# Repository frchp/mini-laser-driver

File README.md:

# mini-laser-driver

## Goal
300mA capable constant current source driver for laser diode application.

## Repository

[hw](hw/) : Hardware sources

[sim](sim/) : LTSpice simulation

[doc](doc/) : Useful documentation

[results](results/) : Measurements

## Results
TODO

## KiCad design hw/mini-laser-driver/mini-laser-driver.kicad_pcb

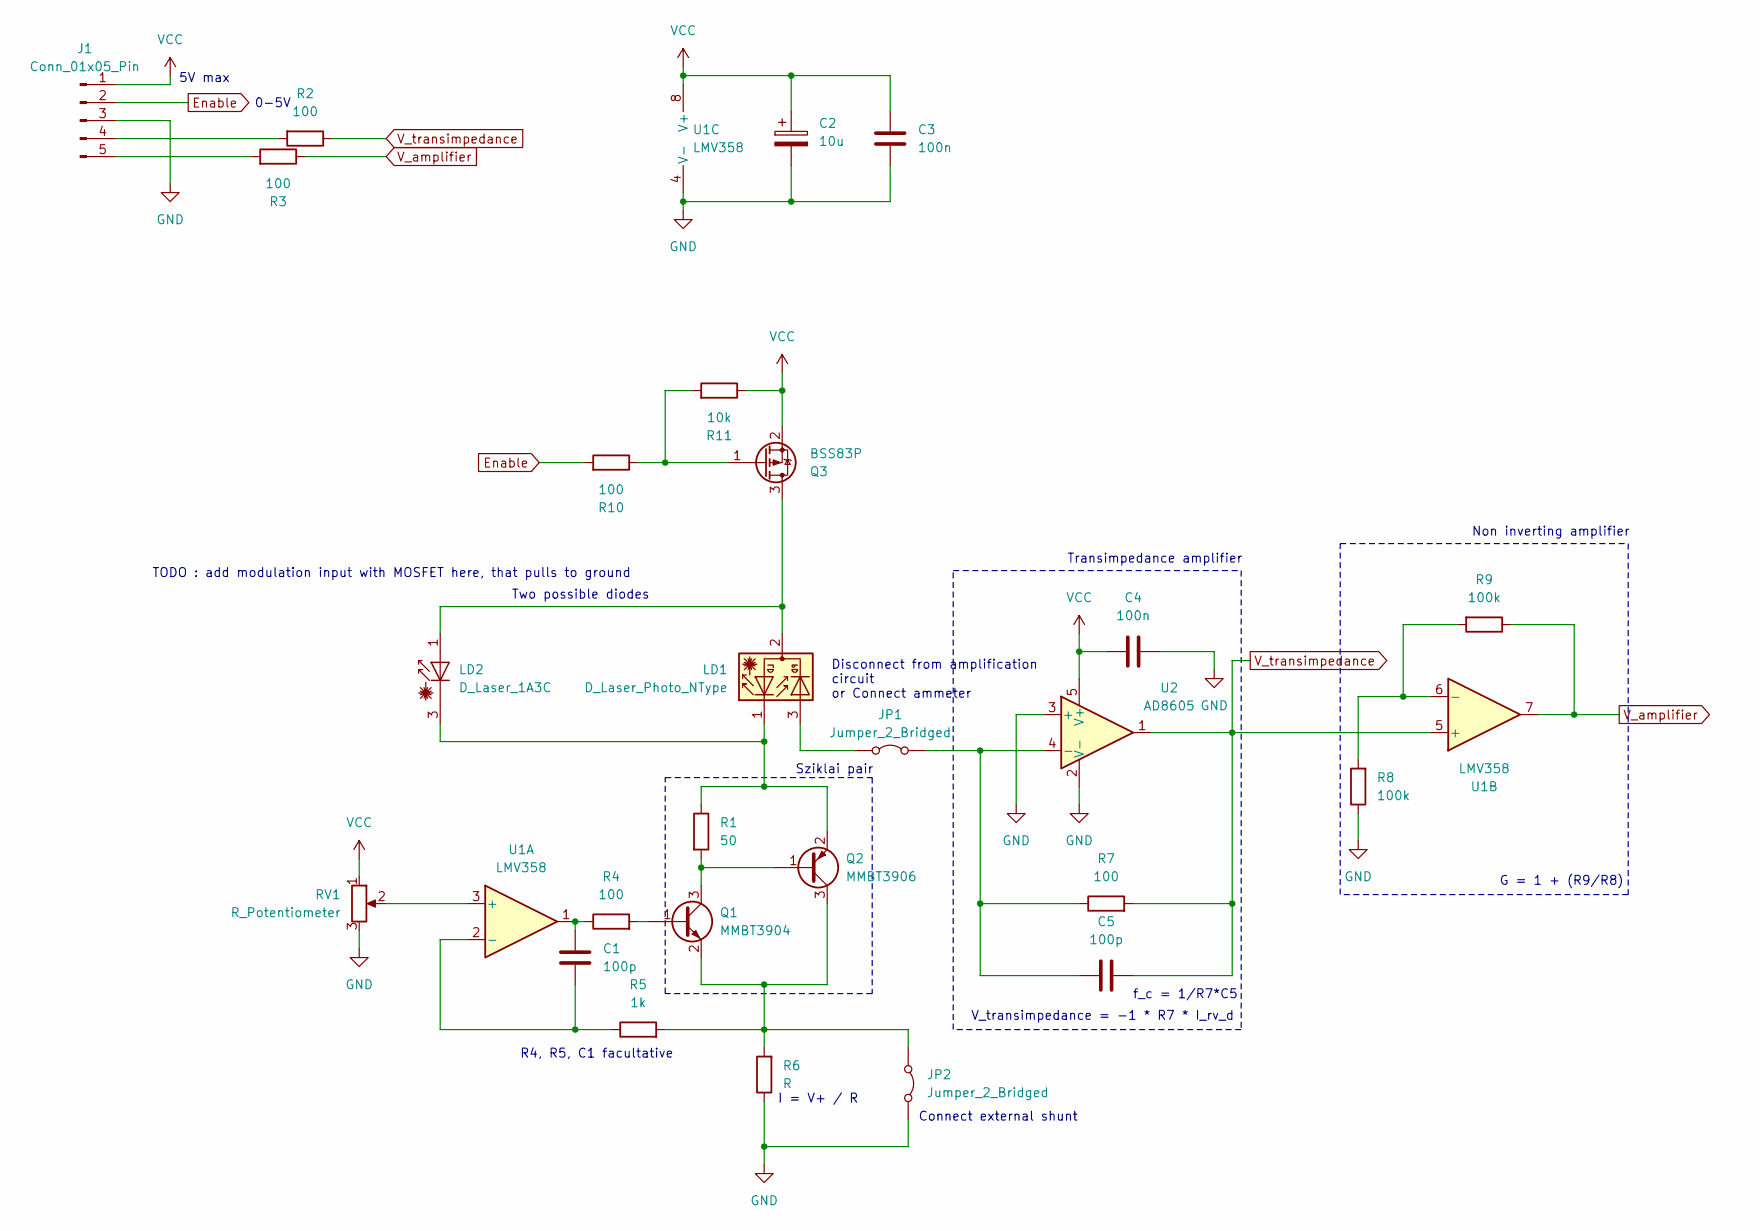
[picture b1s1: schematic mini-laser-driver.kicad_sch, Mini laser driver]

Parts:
C1, C5: 100p; C_0603_1608Metric_Pad1.08x0.95mm_HandSolder
C2: 10u; CP_Radial_D4.0mm_P2.00mm
C3, C4: 100n; C_0603_1608Metric_Pad1.08x0.95mm_HandSolder
J1: Conn_01x05_Pin; PinHeader_1x05_P2.54mm_Vertical
JP1, JP2: Jumper_2_Bridged; PinHeader_1x02_P2.54mm_Vertical
LD1: D_Laser_Photo_NType; TO-18-3_Window
LD2: D_Laser_1A3C; TO-18-3_Window
Q1: MMBT3904; SOT-23
Q2: MMBT3906; SOT-23
Q3: BSS83P; SOT-23
R1: 50; R_0603_1608Metric_Pad0.98x0.95mm_HandSolder
R2, R3, R4, R7, R10: 100; R_0603_1608Metric_Pad0.98x0.95mm_HandSolder
R5: 1k; R_0603_1608Metric_Pad0.98x0.95mm_HandSolder
R6: R; R_1206_3216Metric_Pad1.30x1.75mm_HandSolder
R8, R9: 100k; R_0603_1608Metric_Pad0.98x0.95mm_HandSolder
R11: 10k; R_0603_1608Metric_Pad0.98x0.95mm_HandSolder
RV1: R_Potentiometer; Potentiometer_Bourns_3296W_Vertical
U1: LMV358; SOIC-8_3.9x4.9mm_P1.27mm
U2: AD8605; TSOT-23-5

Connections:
Enable: J1.2, R10.2
GND: C2.2, C3.2, C4.2, J1.3, JP2.2 (B), R6.1, R8.1, RV1.3, U1.4 (V-), U2.2 (V-), U2.3 (+)
unnamed: C1.1, R4.1, U1.1
unnamed: J1.4, R2.2
unnamed: J1.5, R3.2
unnamed: JP1.1 (A), LD1.3
unnamed: C5.1, JP1.2 (B), R7.1, U2.4 (-)
unnamed: JP2.1 (A), Q1.2 (E), Q2.3 (C), R5.2, R6.2
unnamed: LD1.2, LD2.1 (A), Q3.3 (D)
unnamed: LD1.1, LD2.3 (K), Q2.2 (E), R1.1
unnamed: Q1.1 (B), R4.2
unnamed: Q1.3 (C), Q2.1 (B), R1.2
unnamed: Q3.1 (G), R10.1, R11.2
unnamed: RV1.2, U1.3 (+)
unnamed: C1.2, R5.1, U1.2 (-)
unnamed: R8.2, R9.2, U1.6 (-)
VCC: C2.1, C3.1, C4.1, J1.1, Q3.2 (S), R11.1, RV1.1, U1.8 (V+), U2.5 (V+)
V_amplifier: R3.1, R9.1, U1.7
V_transimpedance: C5.2, R2.1, R7.2, U1.5 (+), U2.1

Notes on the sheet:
I = V+ / R
R4, R5, C1 facultative
5V max
G = 1 + (R9/R8)
Two possible diodes
f_c = 1/R7*C5
V_transimpedance = -1 * R7 * I_rv_d
Disconnect from amplification circuit or Connect ammeter
Sziklai pair
Connect external shunt
0-5V
Non inverting amplifier
Transimpedance amplifier
TODO : add modulation input with MOSFET here, that pulls to ground

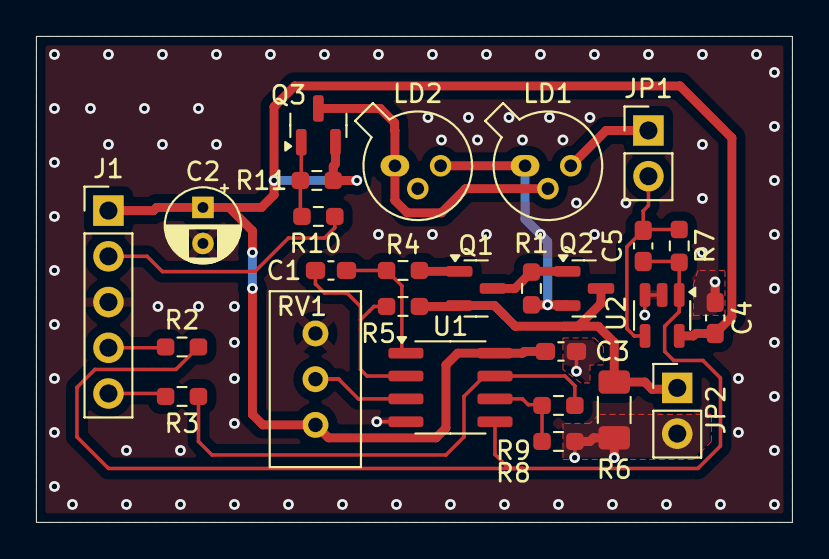
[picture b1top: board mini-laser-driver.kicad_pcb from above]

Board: 2 copper layers, 42.0 x 27.0 mm, 27 parts (0 on the bottom side), 19 nets.

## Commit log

2025-02-06 Add initial files and tree structure
2025-02-06 Added circuit simulation
2025-02-06 Added SCH + PCB
2025-02-06 Added PDF schematic
2025-02-06 Add fab files
2025-02-07 Add some doc and my legacy projects
2025-02-07 Rename versions to concordate with what is written in schematic
